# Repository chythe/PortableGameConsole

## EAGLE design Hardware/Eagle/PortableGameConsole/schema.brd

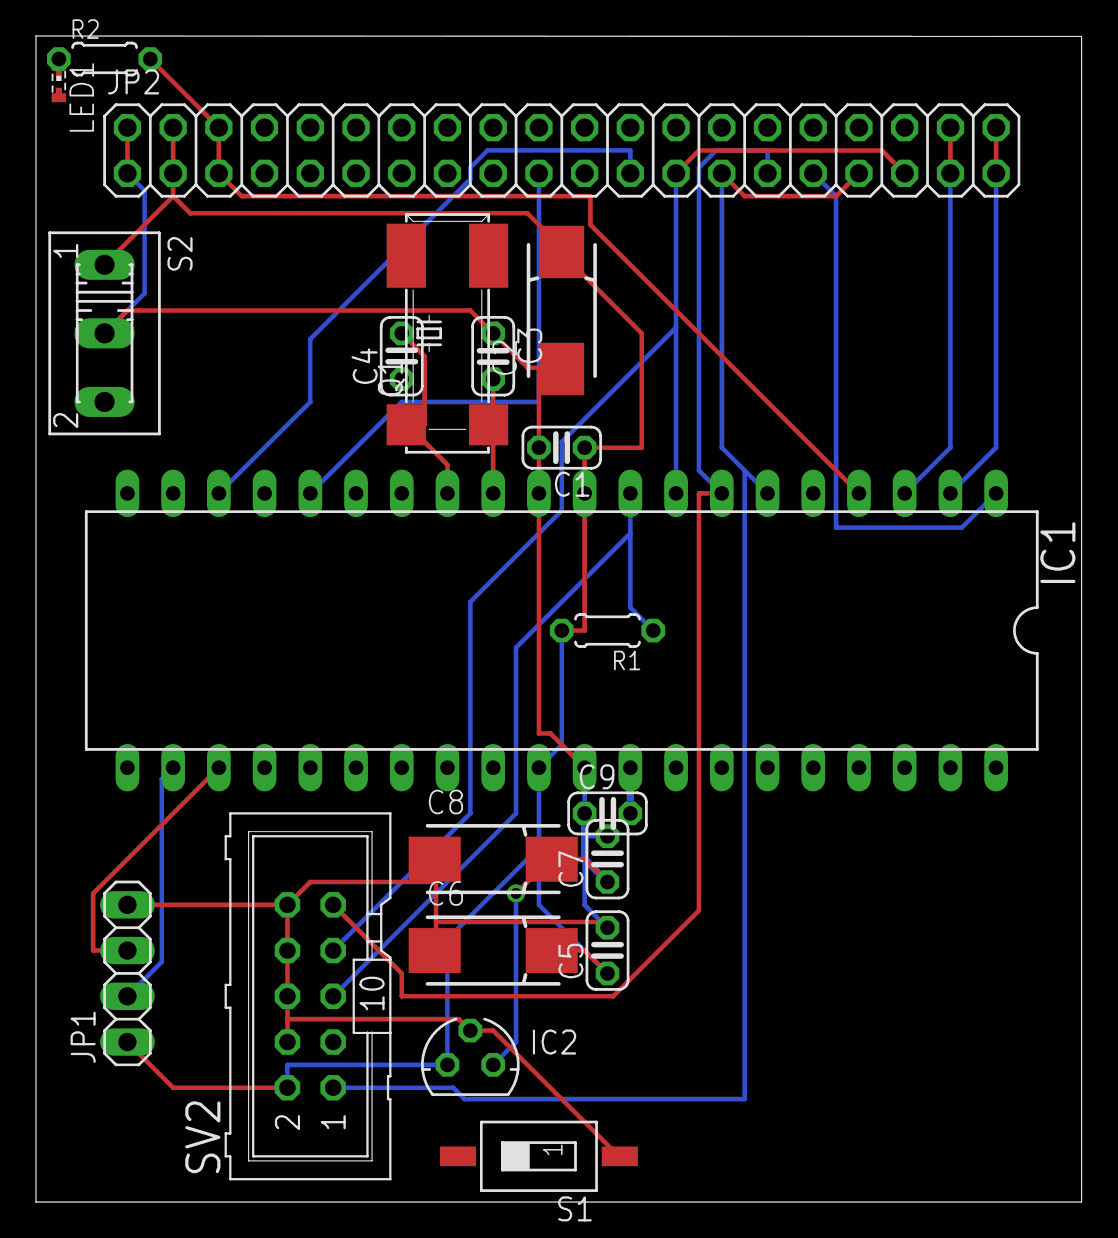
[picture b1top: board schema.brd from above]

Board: 2 copper layers, 58.1 x 64.8 mm, 20 parts (0 on the bottom side), 18 nets.

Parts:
C1, C5, C7, C9: 100nF; C025-024X044
C2: 22μF; 085CS_1AR
C3, C4: 22pF; C025-024X044
C6, C8: 47μF; 085CS_1AR
IC1: MEGA16-P; DIL40
IC2: 3,3V; 78LXX
JP1: 1X04
JP2: 2X20
LED1: SMARTLED-TTW
Q1: 16MHz; 86SMX
R1: 10KΩ; 0204/5
R2: 100Ω; 0204/5
S1: ON/OFF; SMS-001
S2: 255SB
SV2: ML10

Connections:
GND: C1.2, C2.-, C3.1, C5.2, C6.-, C7.1, C7.2, C8.+, C8.-, C9.1, IC1.11, IC1.31, IC2.GND, IC2.IN, JP1.4, JP2.1, JP2.2, LED1.C@1, S1.1, S2.2, SV2.4, SV2.6, SV2.8, SV2.10
LCD_CS: IC1.3, JP2.37, JP2.38
LCD_PWM: IC1.4, JP2.5, JP2.6, R2.2
LCD_RS: IC1.2, JP2.39, JP2.40
LCD_RST: IC1.1, JP2.31
MISO: IC1.7, JP2.29, SV2.9
MOSI: IC1.6, JP2.27, JP2.33, SV2.1
unnamed: LED1.A@1, R2.1
RST: IC1.9, R1.1, SV2.5
S$1: C9.2, IC1.32
SCK: IC1.8, JP2.25, JP2.35, SV2.7
SCL: IC1.22, JP1.2
SDA: IC1.23, JP1.3
T_CS: IC1.18, JP2.23
T_INT: IC1.16, JP2.19
VCC: C1.1, C2.+, C5.1, C6.+, IC1.10, IC1.30, IC2.OUT, JP1.1, JP2.3, JP2.4, R1.2, S2.1, SV2.2
XTAL1: C4.2, IC1.13, Q1.4
XTAL2: C3.2, IC1.12, Q1.1

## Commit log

2019-07-31 adding all files
